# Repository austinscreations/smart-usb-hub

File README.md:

# smart-usb-hub
a custom usb hub for tinkers that can interface with smart home systems and provide data on power usage of a device.

2020-10-08 
added CAD files for usb2.0 for those who may want to 3d print their own case

2020-08-27
version 2 is created, has 4 usb ports, mosfet is rated for 3 amps, external power supply notifies the MCU which can allow increased current alotment in programming. eg: max 500ma under usb input vs max 5A (shared by all ports) under power supply usage (current limited by dc-dc converter)

INA219 shunt is 0.1ohm 2W 1% toleance which allows for sense current up to 3.2Amps.

version 2 now includes 4 ports using usb2514 for hub control.

board allows for buttons to be placed and allows for software control of outputs -- newpixels give the ability to iniicate status of ports. 4 pin header spot has been added for the use of an I2C LCD.

current design allows for various arengments of a custom 3D printed case that allows the hub to me mounted in various ways

current board size is 100*75mm

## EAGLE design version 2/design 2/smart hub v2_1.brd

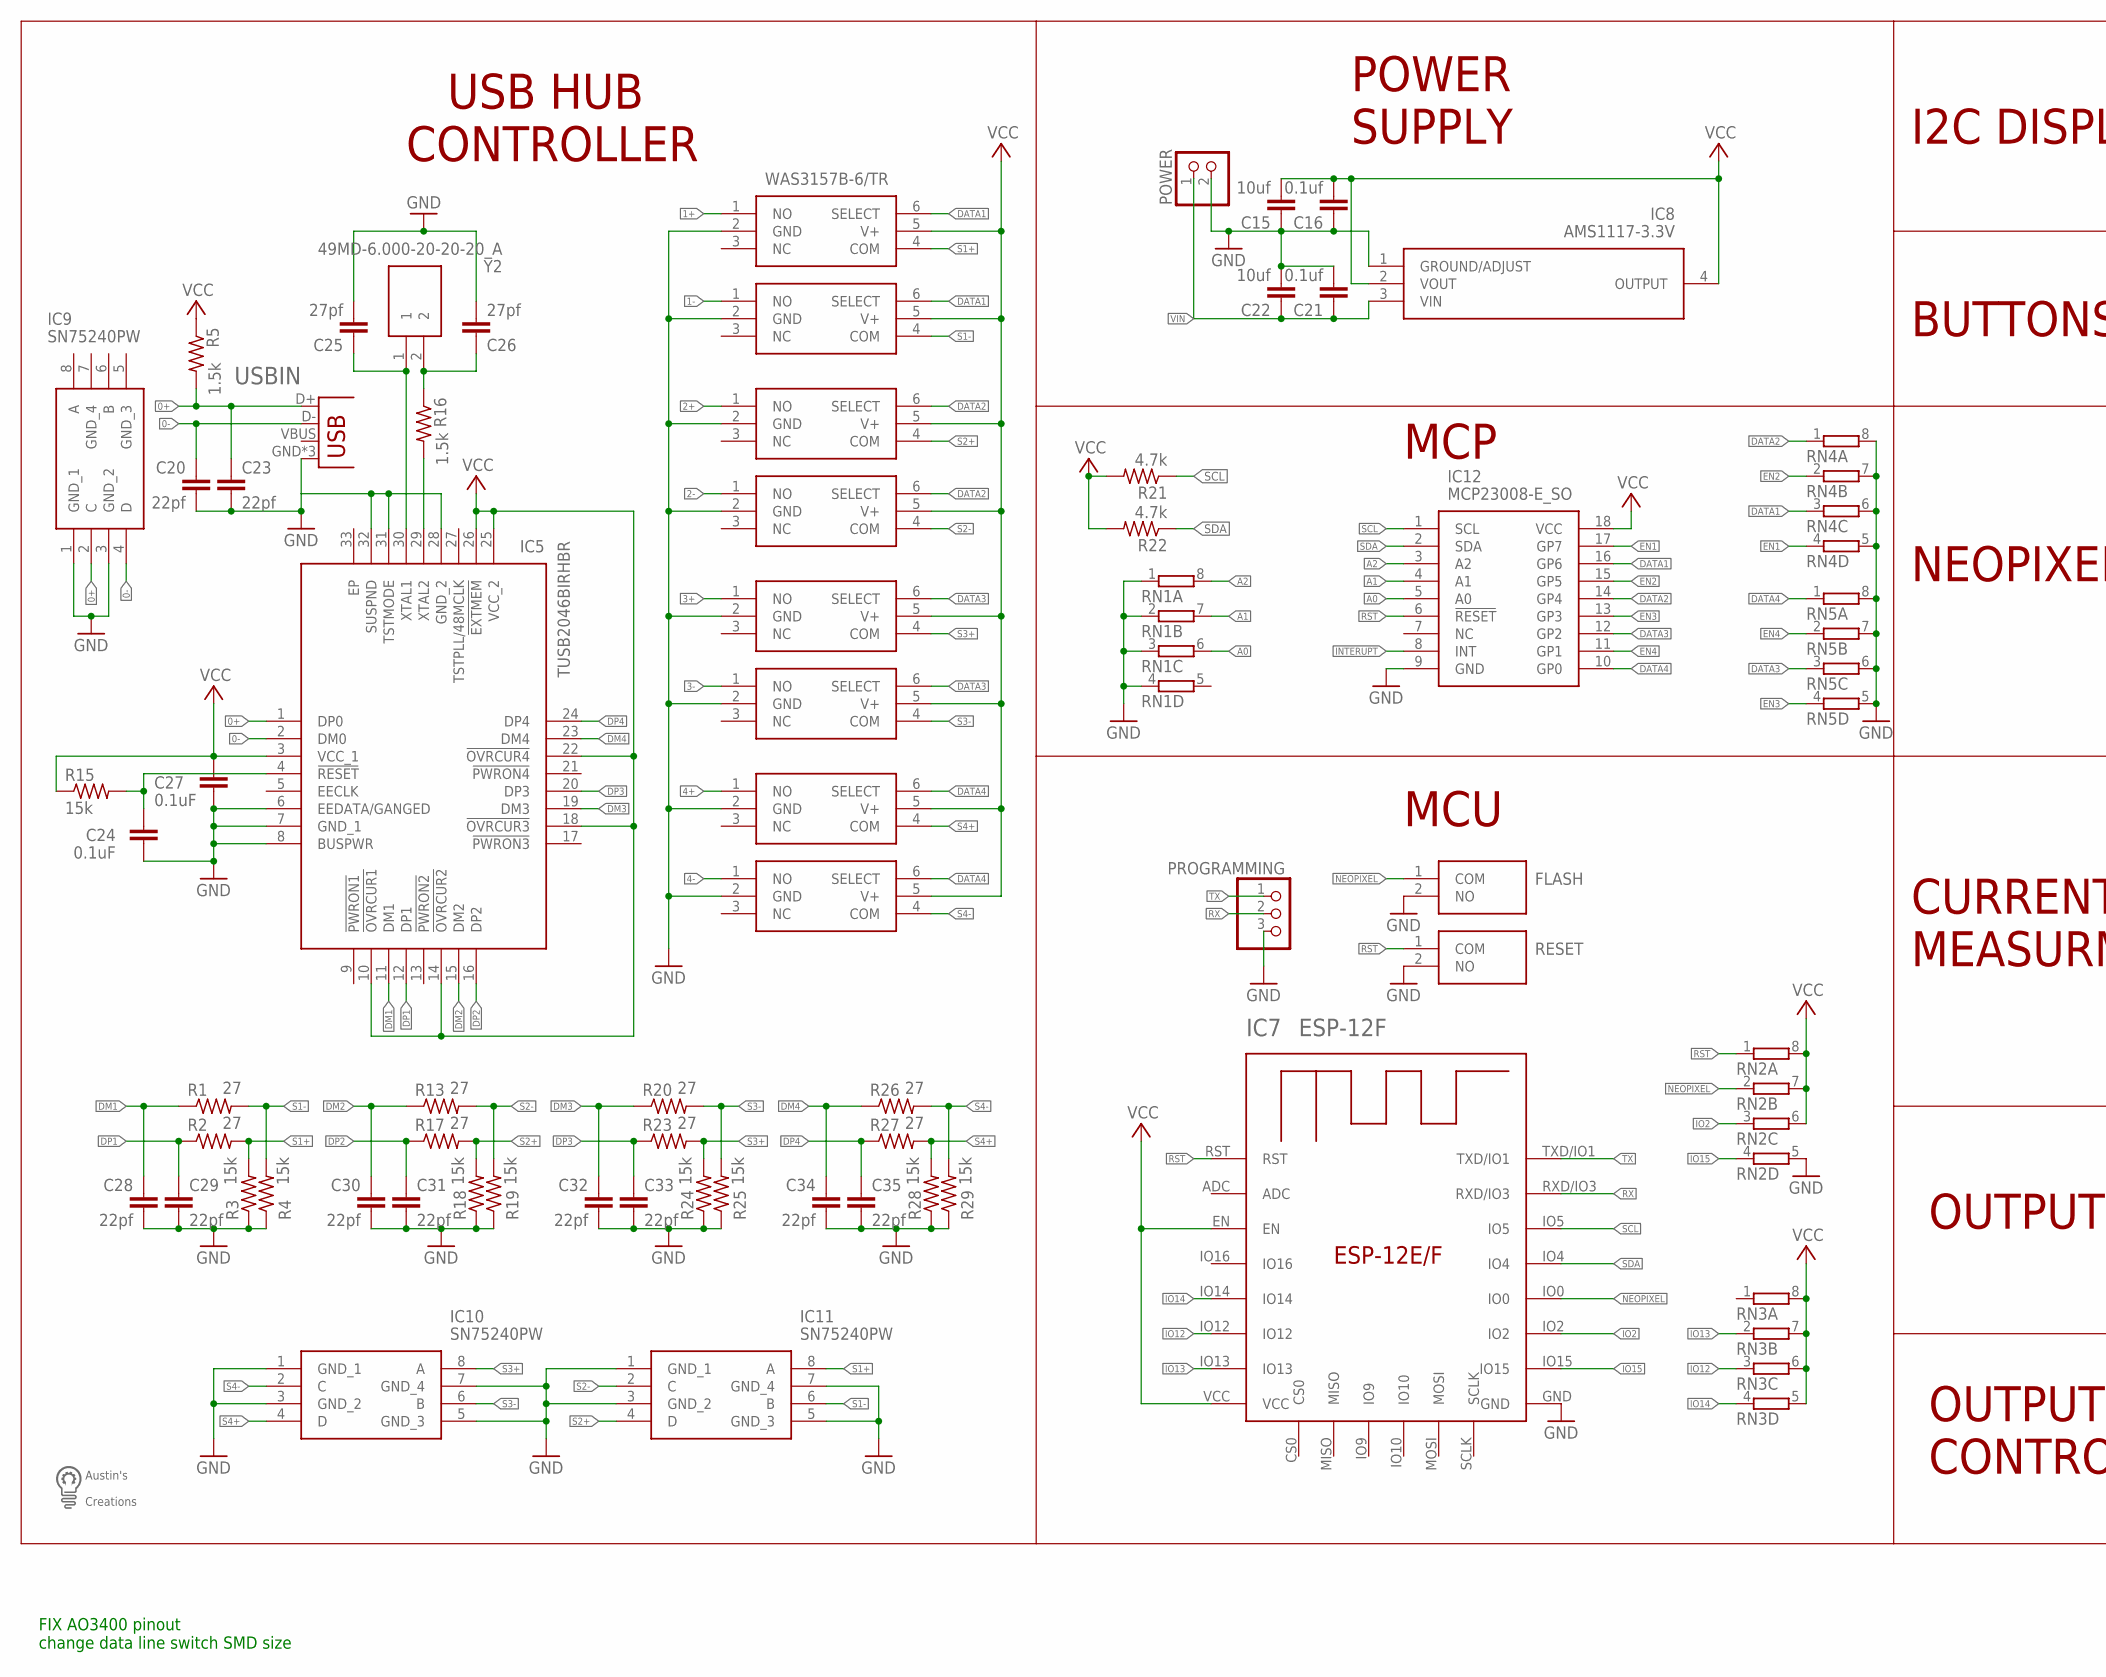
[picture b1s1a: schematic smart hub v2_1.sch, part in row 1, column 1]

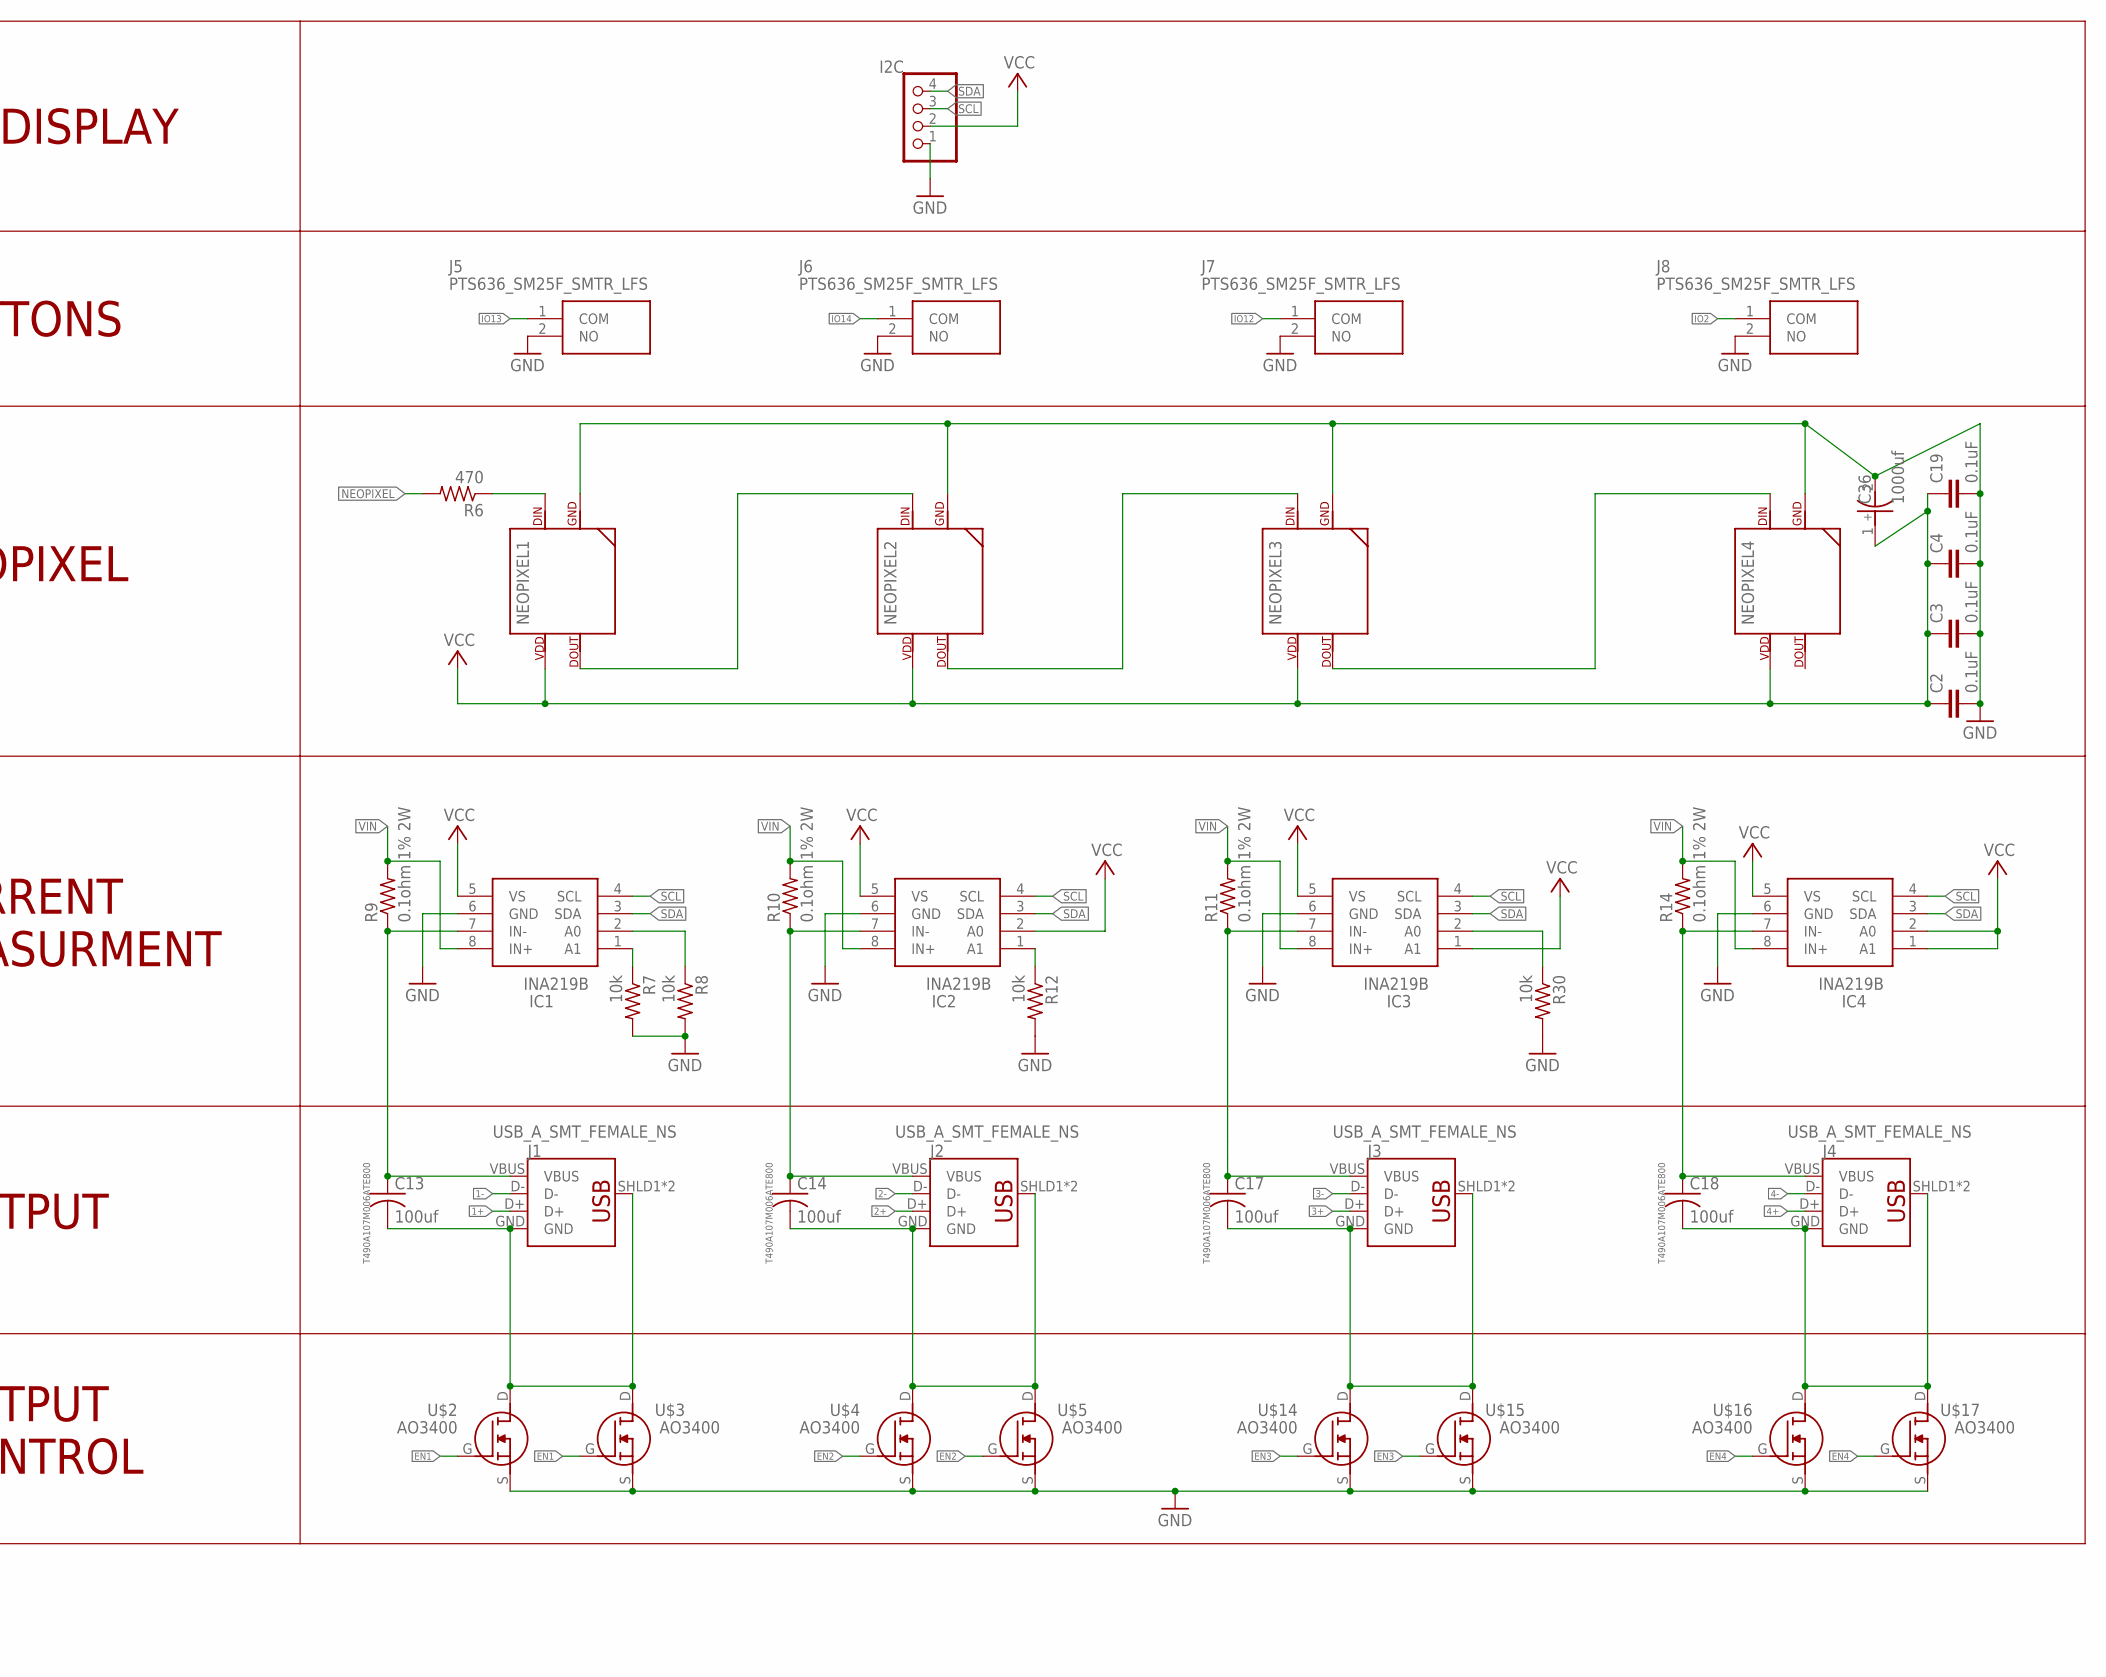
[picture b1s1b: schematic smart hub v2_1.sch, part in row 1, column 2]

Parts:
C2, C3, C4, C19, C24, C27: 0.1uF; C0603
C13, C14, C17, C18: 100uf; C1206
C15, C22: 10uf; C0603
C16, C21: 0.1uf; C0603
C20, C23, C28, C29, C30, C31, C32, C33, C34, C35: 22pf; C0603
C25, C26: 27pf; C0603
C36: 1000uf; CAPAE1030X1050N
FLASH: PTS636_SM25F_SMTR_LFS; PTS636SM25FSMTRLFS
I2C: PINHD-1X4; 1X04
IC1, IC2, IC3, IC4: INA219B; SOIC127P600X175-8N
IC5: TUSB2046BIRHBR; QFN50P500X500X100-33N
IC7: ESP-12F; ESP-12E
IC8: AMS1117-3.3V; SOT229P700X180-4N
IC9, IC10, IC11: SN75240PW; SOP65P640X120-8N
IC12: MCP23008-E_SO; SOIC127P1030X265-18N
J1, J2, J3, J4: USB_A_SMT_FEMALE_NS; USB-A-S-NOSILK-FEMALE
J5, J6, J7, J8: PTS636_SM25F_SMTR_LFS; PTS636SM25FSMTRLFS
NEOPIXEL1, NEOPIXEL2, NEOPIXEL3, NEOPIXEL4: SK6812NEOPIXEL5050; SK6812
POWER: PINHD-1X2; 1X02
PROGRAMMING: PINHD-1X3; 1X03
R1, R2, R13, R17, R20, R23, R26, R27: 27; R0603
R3, R4, R15, R18, R19, R24, R25, R28, R29: 15k; R0603
R5, R16: 1.5k; R0603
R6: 470; R0603
R7, R8, R12, R30: 10k; R0603
R9, R10, R11, R14: 0.1ohm 1% 2W; R2512W
R21, R22: 4.7k; R0603
RESET: PTS636_SM25F_SMTR_LFS; PTS636SM25FSMTRLFS
RN1, RN2, RN3, RN4, RN5: 4R-N0603-ARC; 0603-ARC
U$1: LOGOMASSIVE
U$2, U$3, U$4, U$5, U$14, U$15, U$16, U$17: AO3400
U$6, U$7, U$8, U$9, U$10, U$11, U$12, U$13: WAS3157B-6/TR
USBIN: USB-MICROB
Y2: 49MD-6.000-20-20-20_A; 49MD6000202020A

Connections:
0+: C23.1, IC5.1 (DP0), IC9.2 (C), R5.2, USBIN.D+
0-: C20.1, IC5.2 (DM0), IC9.4 (D), USBIN.D-
1+: J1.D+, U$6.1 (NO)
1-: J1.D-, U$7.1 (NO)
2+: J2.D+, U$8.1 (NO)
2-: J2.D-, U$9.1 (NO)
3+: J3.D+, U$10.1 (NO)
3-: J3.D-, U$11.1 (NO)
4+: J4.D+, U$12.1 (NO)
4-: J4.D-, U$13.1 (NO)
A0: IC12.5 (A0), RN1.6 (2)
A1: IC12.4 (A1), RN1.7 (2)
A2: IC12.3 (A2), RN1.8 (2)
DATA1: IC12.16 (GP6), RN4.3 (1), U$6.6 (SELECT), U$7.6 (SELECT)
DATA2: IC12.14 (GP4), RN4.1, U$8.6 (SELECT), U$9.6 (SELECT)
DATA3: IC12.12 (GP2), RN5.3 (1), U$10.6 (SELECT), U$11.6 (SELECT)
DATA4: IC12.10 (GP0), RN5.1, U$12.6 (SELECT), U$13.6 (SELECT)
DM1: C28.1, IC5.11 (DM1), R1.1
DM2: C30.1, IC5.15 (DM2), R13.1
DM3: C32.1, IC5.19 (DM3), R20.1
DM4: C34.1, IC5.23 (DM4), R26.1
DP1: C29.1, IC5.12 (DP1), R2.1
DP2: C31.1, IC5.16 (DP2), R17.1
DP3: C33.1, IC5.20 (DP3), R23.1
DP4: C35.1, IC5.24 (DP4), R27.1
EN1: IC12.17 (GP7), RN4.4 (1), U$2.G, U$3.G
EN2: IC12.15 (GP5), RN4.2 (1), U$4.G, U$5.G
EN3: IC12.13 (GP3), RN5.4 (1), U$14.G, U$15.G
EN4: IC12.11 (GP1), RN5.2 (1), U$16.G, U$17.G
GND: C2.2, C3.2, C4.2, C15.1, C16.1, C19.2, C20.2, C21.2, C22.2, C23.2, C24.2, C25.2, C26.2, C27.2, C28.2, C29.2, C30.2, C31.2, C32.2, C33.2, C34.2, C35.2, C36.2 (-), FLASH.2 (NO), I2C.1, IC1.6 (GND), IC2.6 (GND), IC3.6 (GND), IC4.6 (GND), IC5.6 (EEDATA/GANGED), IC5.7 (GND_1), IC5.8 (BUSPWR), IC5.28 (GND_2), IC5.31 (TSTMODE), IC5.32 (SUSPND), IC7.GND, IC8.1 (GROUND/ADJUST), IC9.1 (GND_1), IC9.3 (GND_2), IC10.1 (GND_1), IC10.3 (GND_2), IC10.5 (GND_3), IC10.7 (GND_4), IC11.1 (GND_1), IC11.3 (GND_2), IC11.5 (GND_3), IC11.7 (GND_4), IC12.9 (GND), J5.2 (NO), J6.2 (NO), J7.2 (NO), J8.2 (NO), NEOPIXEL1.3 (GND), NEOPIXEL2.3 (GND), NEOPIXEL3.3 (GND), NEOPIXEL4.3 (GND), POWER.2, PROGRAMMING.3, R3.1, R4.1, R7.2, R8.2, R12.2, R18.1, R19.1, R24.1, R25.1, R28.1, R29.1, R30.2, RESET.2 (NO), RN1.1, RN1.2 (1), RN1.3 (1), RN1.4 (1), RN2.5 (2), RN4.5 (2), RN4.6 (2), RN4.7 (2), RN4.8 (2), RN5.5 (2), RN5.6 (2), RN5.7 (2), RN5.8 (2), U$2.S, U$3.S, U$4.S, U$5.S, U$6.2 (GND), U$7.2 (GND), U$8.2 (GND), U$9.2 (GND), U$10.2 (GND), U$11.2 (GND), U$12.2 (GND), U$13.2 (GND), U$14.S, U$15.S, U$16.S, U$17.S, USBIN.GND, USBIN.MT1 (GND), USBIN.MT2 (GND)
INTERUPT: IC12.8 (INT)
IO2: IC7.IO2, J8.1 (COM), RN2.3 (1)
IO12: IC7.IO12, J7.1 (COM), RN3.3 (1)
IO13: IC7.IO13, J5.1 (COM), RN3.2 (1)
IO14: IC7.IO14, J6.1 (COM), RN3.4 (1)
IO15: IC7.IO15, RN2.4 (1)
unnamed: C13.2, J1.GND, J1.SHLD1 (SHIELD), J1.SHLD2 (SHIELD), U$2.D, U$3.D
unnamed: C14.2, J2.GND, J2.SHLD1 (SHIELD), J2.SHLD2 (SHIELD), U$4.D, U$5.D
unnamed: C25.1, IC5.30 (XTAL1), Y2.1
unnamed: C24.1, IC5.4 (!RESET), R15.2
unnamed: C26.1, R16.1, Y2.2
unnamed: C17.2, J3.GND, J3.SHLD1 (SHIELD), J3.SHLD2 (SHIELD), U$14.D, U$15.D
unnamed: IC5.29 (XTAL2), R16.2
unnamed: NEOPIXEL1.2 (DOUT), NEOPIXEL2.4 (DIN)
unnamed: NEOPIXEL2.2 (DOUT), NEOPIXEL3.4 (DIN)
unnamed: C18.2, J4.GND, J4.SHLD1 (SHIELD), J4.SHLD2 (SHIELD), U$16.D, U$17.D
unnamed: IC3.2 (A0), R30.1
unnamed: IC2.1 (A1), R12.1
unnamed: IC1.1 (A1), R7.1
unnamed: IC1.2 (A0), R8.1
unnamed: NEOPIXEL1.4 (DIN), R6.1
unnamed: C13.1, IC1.7 (IN-), J1.VBUS, R9.1
unnamed: NEOPIXEL3.2 (DOUT), NEOPIXEL4.4 (DIN)
unnamed: C14.1, IC2.7 (IN-), J2.VBUS, R10.1
unnamed: C17.1, IC3.7 (IN-), J3.VBUS, R11.1
unnamed: C18.1, IC4.7 (IN-), J4.VBUS, R14.1
NEOPIXEL: FLASH.1 (COM), IC7.IO0, R6.2, RN2.2 (1)
RST: IC7.RST, IC12.6 (!RESET), RESET.1 (COM), RN2.1
RX: IC7.RXD/IO3, PROGRAMMING.2
S1+: IC11.8 (A), R2.2, R3.2, U$6.4 (COM)
S1-: IC11.6 (B), R1.2, R4.2, U$7.4 (COM)
S2+: IC11.4 (D), R17.2, R18.2, U$8.4 (COM)
S2-: IC11.2 (C), R13.2, R19.2, U$9.4 (COM)
S3+: IC10.8 (A), R23.2, R24.2, U$10.4 (COM)
S3-: IC10.6 (B), R20.2, R25.2, U$11.4 (COM)
S4+: IC10.4 (D), R27.2, R28.2, U$12.4 (COM)
S4-: IC10.2 (C), R26.2, R29.2, U$13.4 (COM)
SCL: I2C.3, IC1.4 (SCL), IC2.4 (SCL), IC3.4 (SCL), IC4.4 (SCL), IC7.IO5, IC12.1 (SCL), R21.1
SDA: I2C.4, IC1.3 (SDA), IC2.3 (SDA), IC3.3 (SDA), IC4.3 (SDA), IC7.IO4, IC12.2 (SDA), R22.1
TX: IC7.TXD/IO1, PROGRAMMING.1
VCC: C2.1, C3.1, C4.1, C15.2, C16.2, C19.1, C27.1, C36.1 (+), I2C.2, IC1.5 (VS), IC2.2 (A0), IC2.5 (VS), IC3.1 (A1), IC3.5 (VS), IC4.1 (A1), IC4.2 (A0), IC4.5 (VS), IC5.3 (VCC_1), IC5.10 (!OVRCUR1), IC5.14 (!OVRCUR2), IC5.18 (!OVRCUR3), IC5.22 (!OVRCUR4), IC5.25 (VCC_2), IC5.26 (!EXTMEM), IC7.EN, IC7.VCC, IC8.2 (VOUT), IC8.4 (OUTPUT), IC12.18 (VCC), NEOPIXEL1.1 (VDD), NEOPIXEL2.1 (VDD), NEOPIXEL3.1 (VDD), NEOPIXEL4.1 (VDD), R5.1, R15.1, R21.2, R22.2, RN2.6 (2), RN2.7 (2), RN2.8 (2), RN3.5 (2), RN3.6 (2), RN3.7 (2), RN3.8 (2), U$6.5 (V+), U$7.5 (V+), U$8.5 (V+), U$9.5 (V+), U$10.5 (V+), U$11.5 (V+), U$12.5 (V+), U$13.5 (V+)
VIN: C21.1, C22.1, IC1.8 (IN+), IC2.8 (IN+), IC3.8 (IN+), IC4.8 (IN+), IC8.3 (VIN), POWER.1, R9.2, R10.2, R11.2, R14.2

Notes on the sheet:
I2C DISPLAY
BUTTONS
NEOPIXEL
CURRENT MEASURMENT
OUTPUT CONTROL
OUTPUT
POWER SUPPLY
USB HUB CONTROLLER
MCU
MCP
T490A107M006ATE800
FIX AO3400 pinout change data line switch SMD size

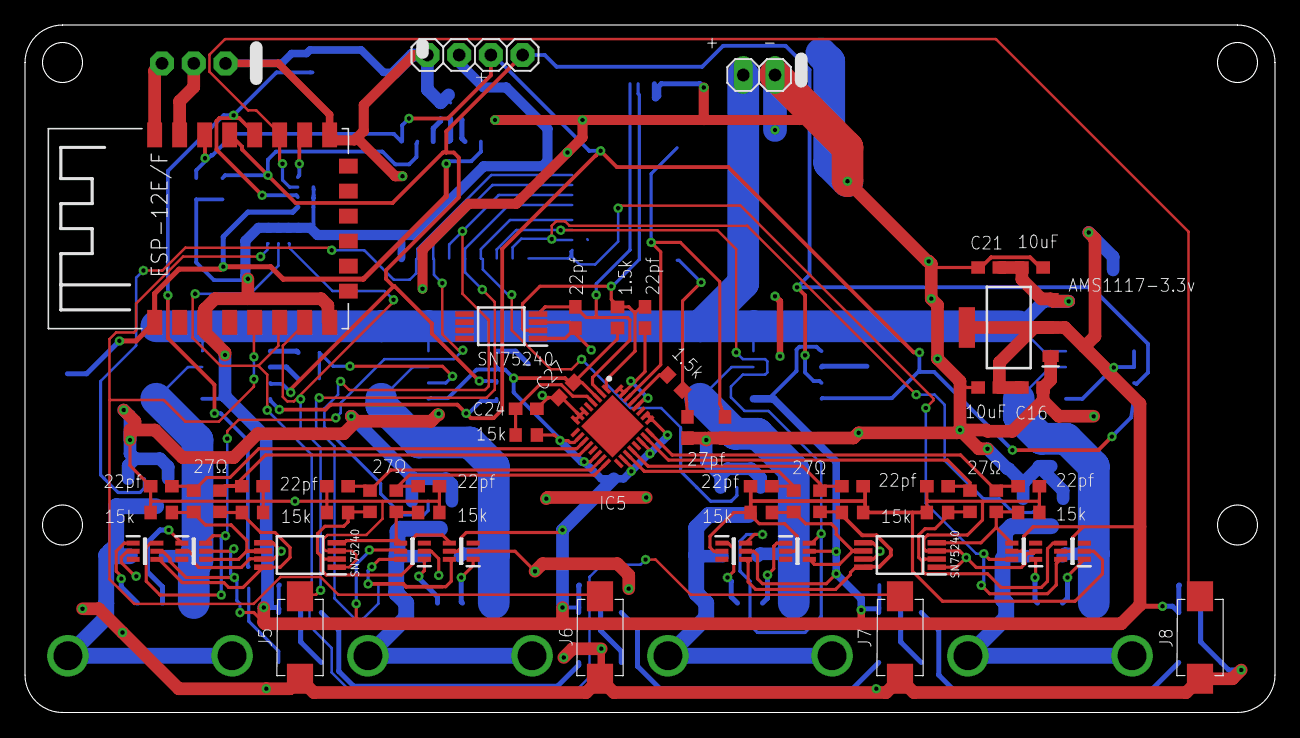
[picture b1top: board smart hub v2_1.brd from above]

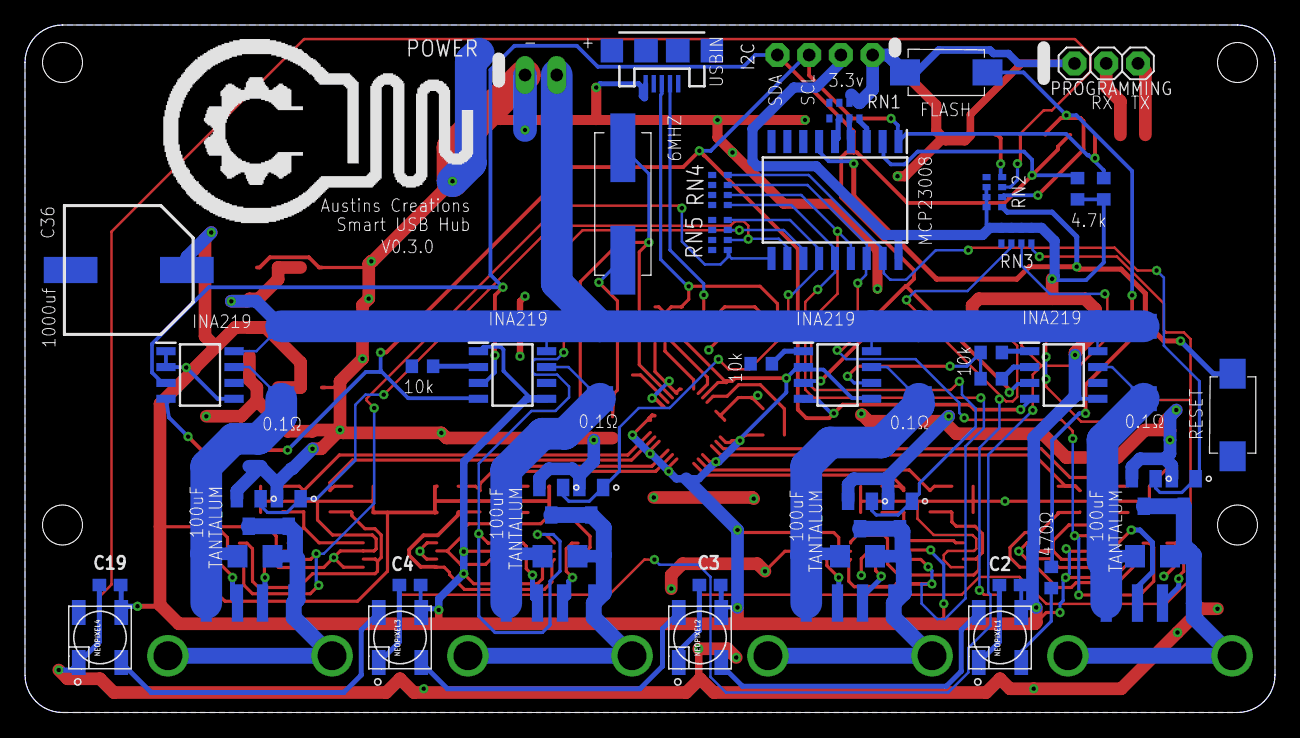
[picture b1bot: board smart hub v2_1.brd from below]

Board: 2 copper layers, 100.0 x 55.0 mm, 109 parts (52 on the bottom side), 71 nets.

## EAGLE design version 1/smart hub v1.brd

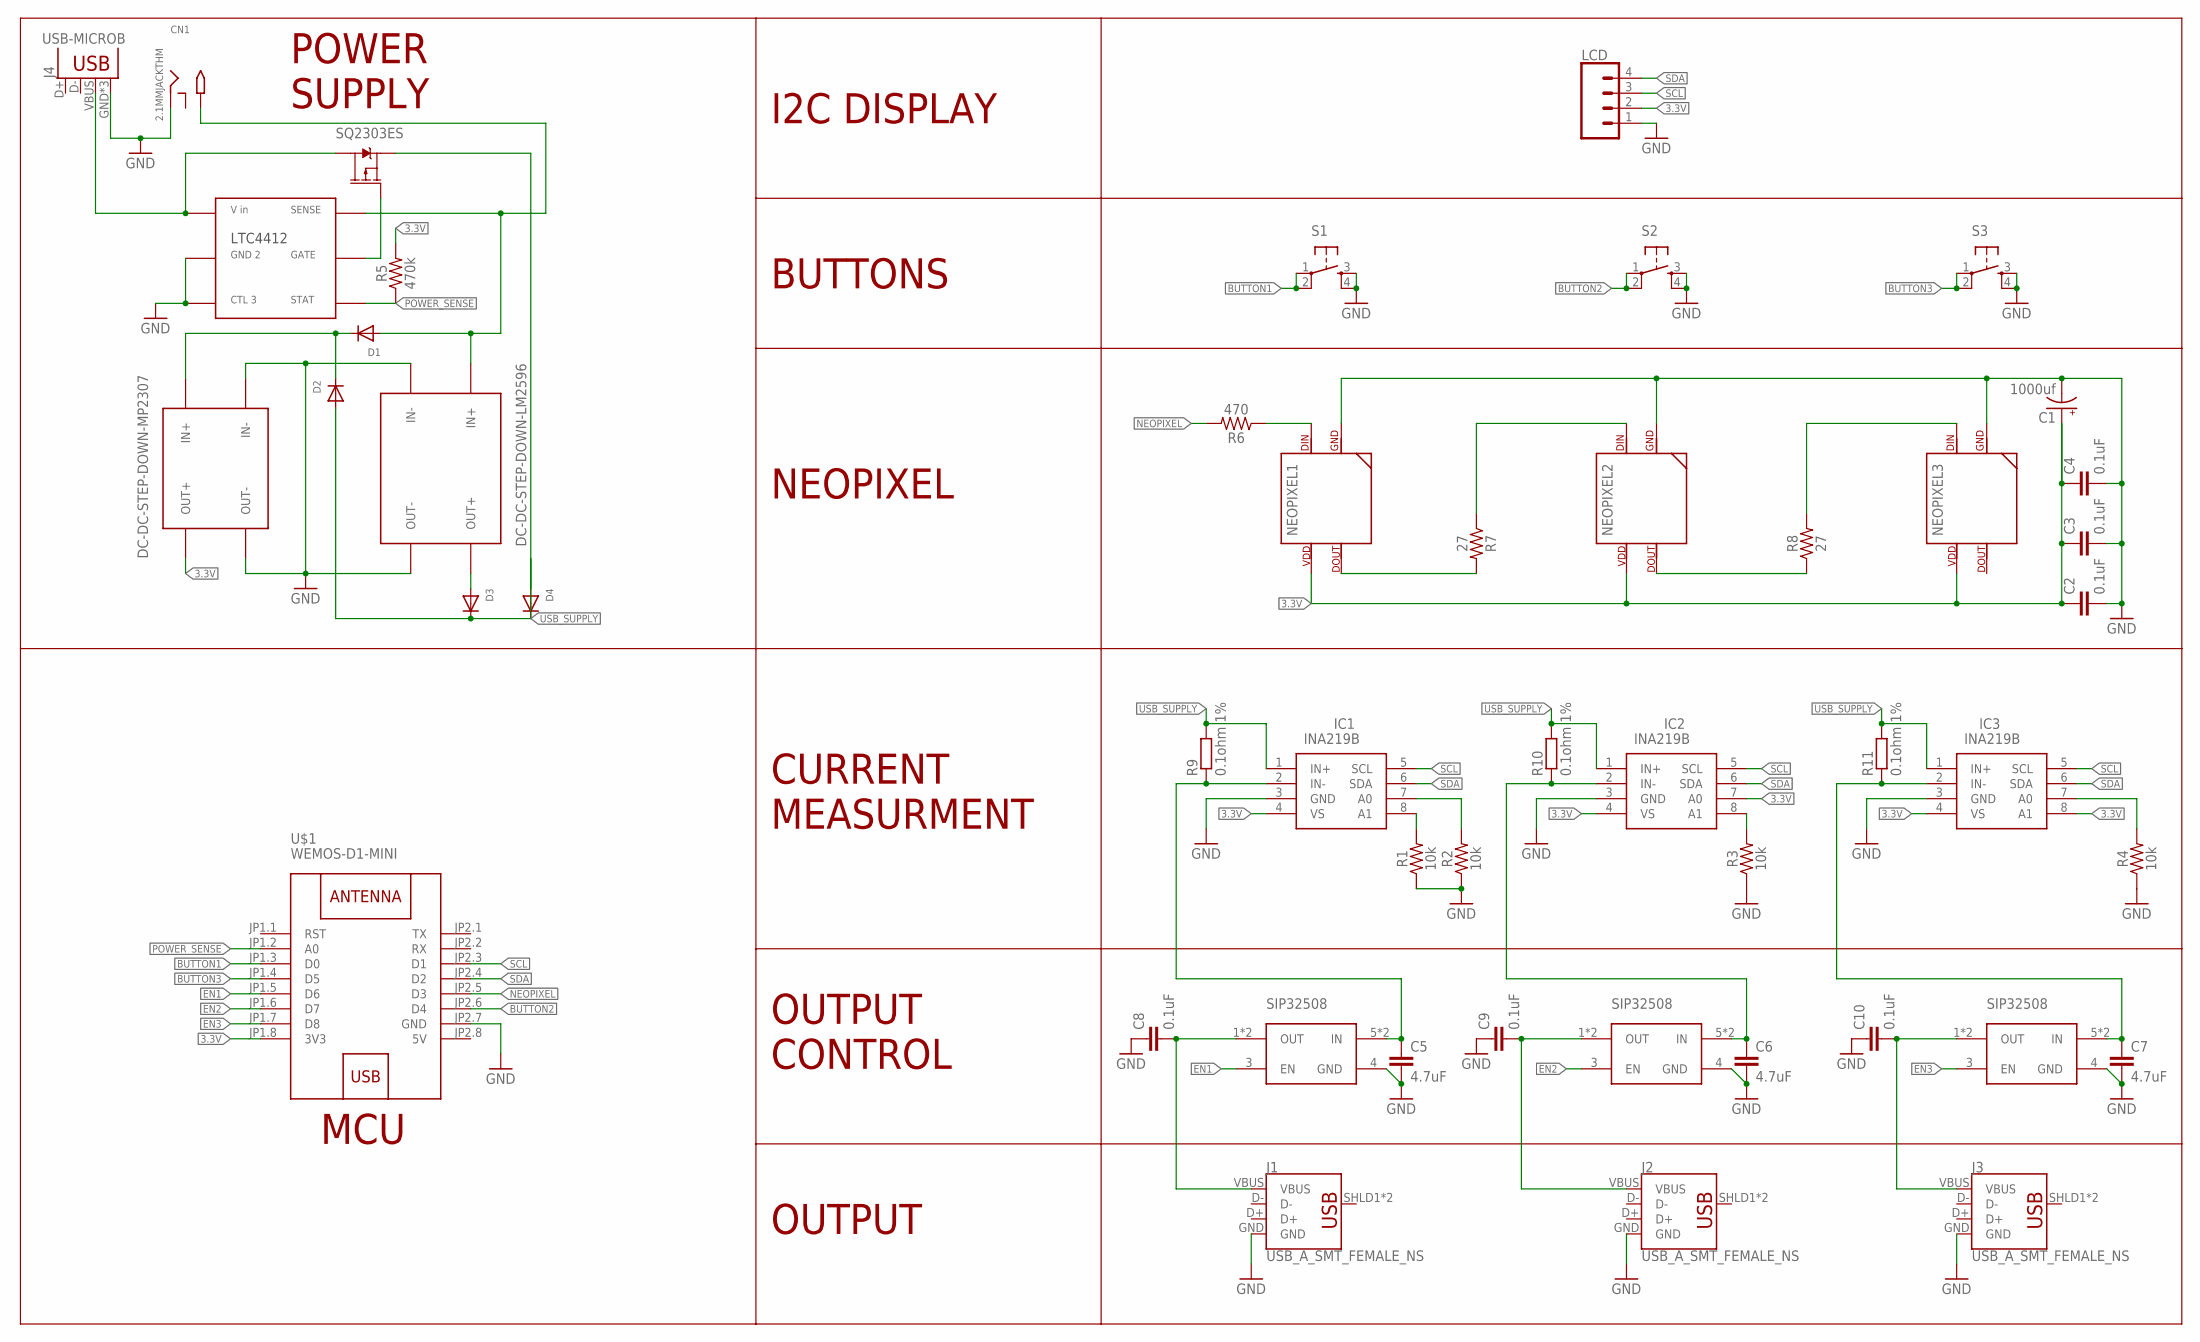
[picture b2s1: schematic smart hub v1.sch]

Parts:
C1: 1000uf; CPOL-RADIAL-5MM-10MM-KIT
C2, C3, C4, C8, C9, C10: 0.1uF; 0603
C5, C6, C7: 4.7uF; 0603
CN1: 2.1MMJACKTHM; PJ-102A
D1, D2, D3, D4: DIODE_SOD-123FL; SOD-123FL
IC1, IC2, IC3: INA219B; SOT65P280X145-8N
J1, J2, J3: USB_A_SMT_FEMALE_NS; USB-A-S-NOSILK-FEMALE
J4: USB-MICROB
LCD: CONN_04; 1X04
LTC4412: LTC4412; TSOT23-6
NEOPIXEL1, NEOPIXEL2, NEOPIXEL3: SK6812NEOPIXEL5050; SK6812
R1, R2, R3, R4: 10k; 0603
R5: 470k; 0603
R6: 470; 0603
R7, R8: 27; 0603
R9, R10, R11: 0.1ohm 1%; R1206W
S1, S2, S3: TAC_SWITCHPTH; TACTILE-PTH
U$1: WEMOS-D1-MINI
U$2: SQ2303ES; SOT23
U$3, U$4, U$5: SIP32508; SOT23-6
U$6: DC-DC-STEP-DOWN-LM2596
U$7: DC-DC-STEP-DOWN-MP2307

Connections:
3.3V: C1.+, C2.1, C3.1, C4.1, IC1.4 (VS), IC2.4 (VS), IC2.7 (A0), IC3.4 (VS), IC3.8 (A1), LCD.2, NEOPIXEL1.1 (VDD), NEOPIXEL2.1 (VDD), NEOPIXEL3.1 (VDD), R5.2, U$1.JP1.8 (3V3), U$7.OUT+
5V: U$1.JP2.8 (5V)
BUTTON1: S1.1, S1.2, U$1.JP1.3 (D0)
BUTTON2: S2.1, S2.2, U$1.JP2.6 (D4)
BUTTON3: S3.1, S3.2, U$1.JP1.4 (D5)
EN1: U$1.JP1.5 (D6), U$3.3 (EN)
EN2: U$1.JP1.6 (D7), U$4.3 (EN)
EN3: U$1.JP1.7 (D8), U$5.3 (EN)
GND: C1.-, C2.2, C3.2, C4.2, C5.2, C6.2, C7.2, C8.1, C9.1, C10.1, CN1.RING, IC1.3 (GND), IC2.3 (GND), IC3.3 (GND), J1.GND, J2.GND, J3.GND, J4.GND, J4.MT1 (GND), J4.MT2 (GND), LCD.1, LTC4412.2, LTC4412.3, NEOPIXEL1.3 (GND), NEOPIXEL2.3 (GND), NEOPIXEL3.3 (GND), R1.1, R2.1, R3.1, R4.1, S1.3, S1.4, S2.3, S2.4, S3.3, S3.4, U$1.JP2.7 (GND), U$3.4 (GND), U$4.4 (GND), U$5.4 (GND), U$6.IN-, U$6.OUT-, U$7.IN-, U$7.OUT-
unnamed: CN1.TIP, D1.A, LTC4412.6, U$6.IN+
unnamed: D1.C, D2.C, U$7.IN+
unnamed: D4.A, U$2.2 (S)
unnamed: D3.A, U$6.OUT+
unnamed: LTC4412.5, U$2.1 (G)
unnamed: NEOPIXEL2.4 (DIN), R7.1
unnamed: J4.VBUS, LTC4412.1, U$2.3 (D)
unnamed: NEOPIXEL3.4 (DIN), R8.2
unnamed: NEOPIXEL1.2 (DOUT), R7.2
unnamed: NEOPIXEL2.2 (DOUT), R8.1
unnamed: C5.1, IC1.2 (IN-), R9.1, U$3.5 (IN), U$3.6 (IN)
unnamed: C6.1, IC2.2 (IN-), R10.1, U$4.5 (IN), U$4.6 (IN)
unnamed: IC3.7 (A0), R4.2
unnamed: IC2.8 (A1), R3.2
unnamed: IC1.8 (A1), R1.2
unnamed: IC1.7 (A0), R2.2
unnamed: NEOPIXEL1.4 (DIN), R6.1
unnamed: C7.1, IC3.2 (IN-), R11.1, U$5.5 (IN), U$5.6 (IN)
unnamed: C8.2, J1.VBUS, U$3.1 (OUT), U$3.2 (OUT)
unnamed: C9.2, J2.VBUS, U$4.1 (OUT), U$4.2 (OUT)
unnamed: C10.2, J3.VBUS, U$5.1 (OUT), U$5.2 (OUT)
NEOPIXEL: R6.2, U$1.JP2.5 (D3)
POWER_SENSE: LTC4412.4, R5.1, U$1.JP1.2 (A0)
SCL: IC1.5 (SCL), IC2.5 (SCL), IC3.5 (SCL), LCD.3, U$1.JP2.3 (D1)
SDA: IC1.6 (SDA), IC2.6 (SDA), IC3.6 (SDA), LCD.4, U$1.JP2.4 (D2)
USB_SUPPLY: D2.A, D3.C, D4.C, IC1.1 (IN+), IC2.1 (IN+), IC3.1 (IN+), R9.2, R10.2, R11.2

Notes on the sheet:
LTC4412
I2C DISPLAY
BUTTONS
NEOPIXEL
CURRENT MEASURMENT
OUTPUT CONTROL
OUTPUT
POWER SUPPLY
MCU

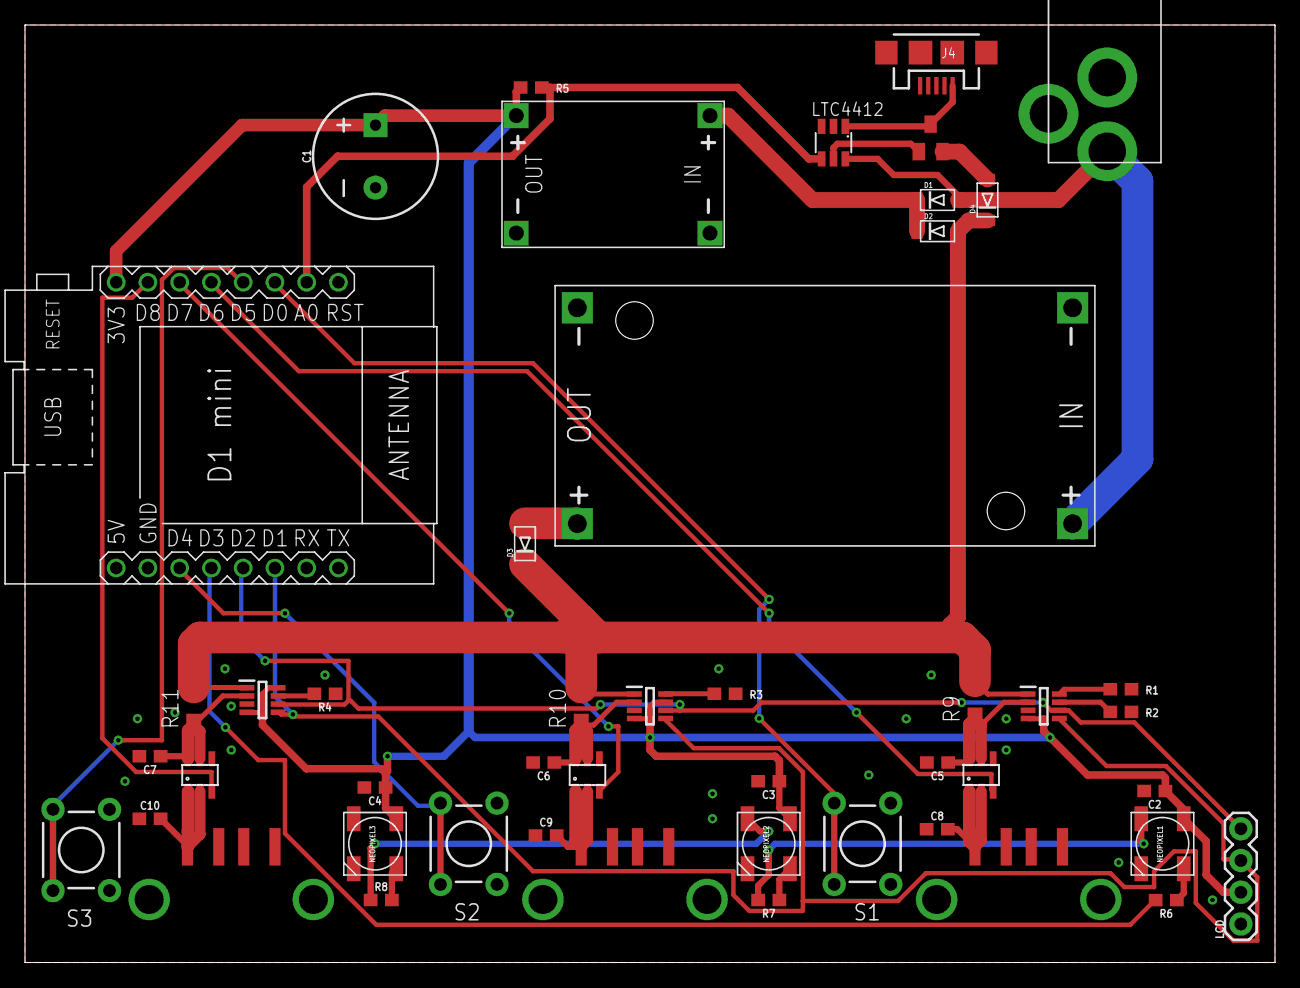
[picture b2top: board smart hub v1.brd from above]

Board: 2 copper layers, 100.0 x 75.0 mm, 48 parts (0 on the bottom side), 34 nets.

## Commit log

2020-08-26 Create info
2020-08-27 Update info
2020-12-04 Create LICENSE

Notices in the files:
parts and their libraries:
SparkFun-Capacitors: Licensing: Creative Commons ShareAlike 4.0 International - https://creativecommons.org/licenses/by-sa/4.0
diy-modules: Released under the Creative Commons Attribution 4.0 International License: http://creativecommons.org/licenses/by/4.0
